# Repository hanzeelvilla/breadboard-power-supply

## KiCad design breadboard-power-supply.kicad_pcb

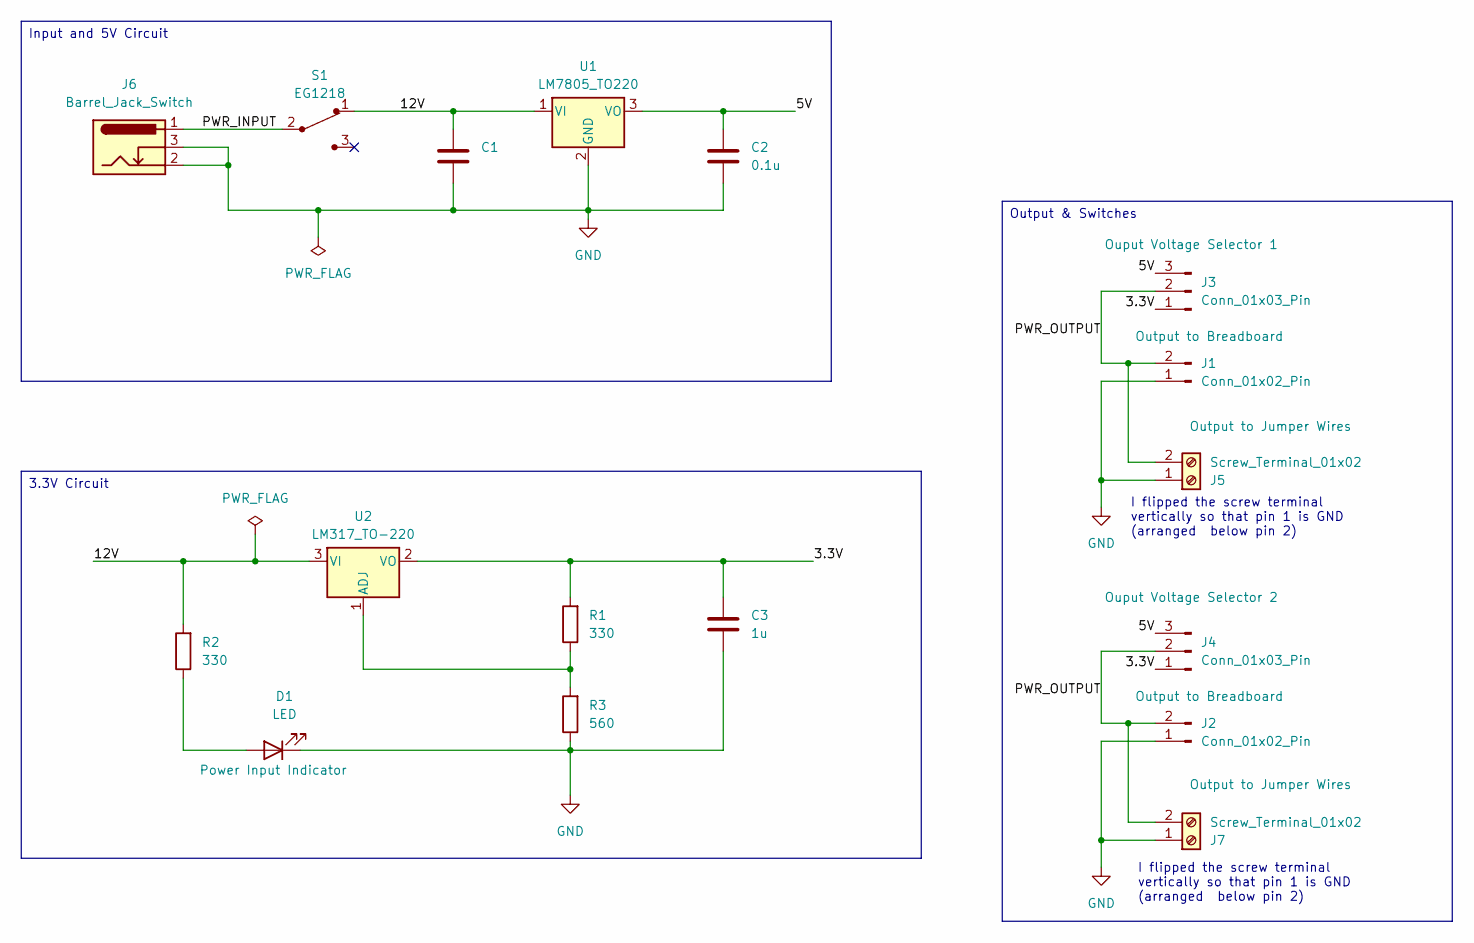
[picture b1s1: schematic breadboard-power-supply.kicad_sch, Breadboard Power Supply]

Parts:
C1: 10u; C_Disc_D3.0mm_W1.6mm_P2.50mm
C2: 0.1u; C_Disc_D3.0mm_W1.6mm_P2.50mm
C3: 1u; C_Disc_D3.0mm_W1.6mm_P2.50mm
D1: LED; LED_D5.0mm
J1, J2: Conn_01x02_Pin; PinHeader_1x02_P2.54mm_Vertical
J3, J4: Conn_01x03_Pin; PinHeader_1x03_P2.54mm_Vertical
J5, J7: Screw_Terminal_01x02; TerminalBlock_Xinya_XY308-2.54-2P_1x02_P2.54mm_Horizontal
J6: Barrel_Jack_Switch; BarrelJack_Horizontal
R1, R2: 330; R_Axial_DIN0204_L3.6mm_D1.6mm_P7.62mm_Horizontal
R3: 560; R_Axial_DIN0204_L3.6mm_D1.6mm_P7.62mm_Horizontal
S1: EG1218; Switch_Slide_11.6x4mm_EG1218; MPN EG1218; Digi-Key_PN EG1903-ND
U1: LM7805_TO220; TO-220-3_Vertical
U2: LM317_TO-220; TO-220-3_Vertical

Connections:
/3.3V: C3.1, J3.1, J4.1, R1.2, U2.2 (VO)
/5V: C2.1, J3.3, J4.3, U1.3 (VO)
/12V: C1.1, R2.2, S1.1, U1.1 (VI), U2.3 (VI)
/PWR_INPUT: J6.1, S1.2
/PWR_OUTPUT: J1.2, J2.2, J3.2, J4.2, J5.2, J7.2
GND: C1.2, C2.2, C3.2, D1.1 (K), J1.1, J2.1, J5.1, J6.2, J6.3, J7.1, R3.1, U1.2 (GND)
unnamed: D1.2 (A), R2.1
unnamed: R1.1, R3.2, U2.1 (ADJ)

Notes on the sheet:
I flipped the screw terminal vertically so that pin 1 is GND (arranged below pin 2)
Input and 5V Circuit
Output & Switches
3.3V Circuit

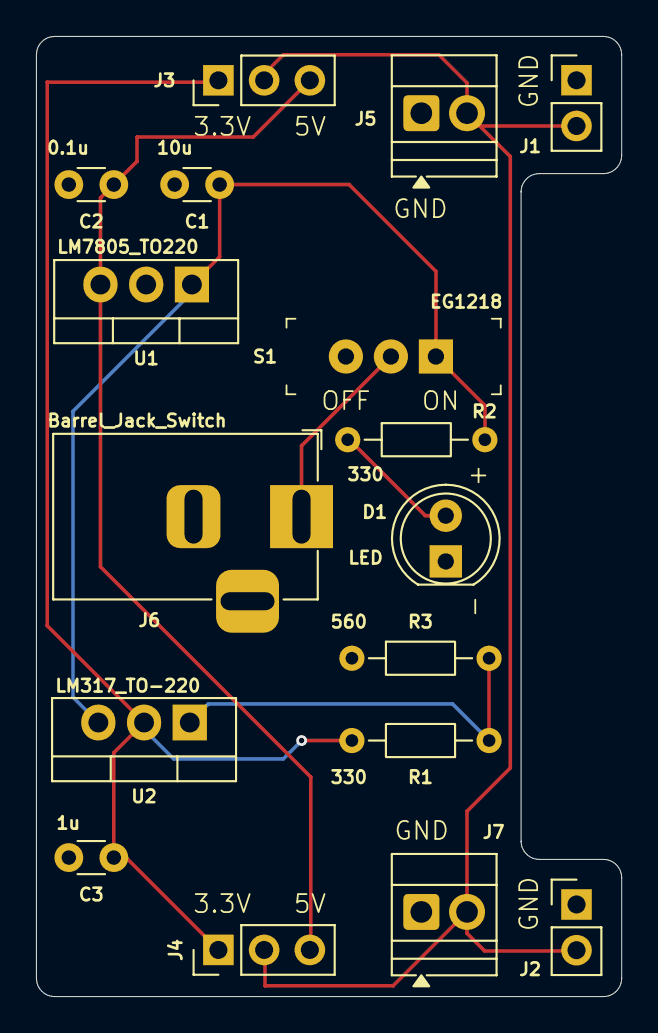
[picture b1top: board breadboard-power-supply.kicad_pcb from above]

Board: 2 copper layers, 32.5 x 53.3 mm, 17 parts (0 on the bottom side), 8 nets.

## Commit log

2025-12-18 Schema finished
2025-12-22 First PCB design
2025-12-22 PCB border refined
2025-12-24 Routes
2025-12-26 Silkscreen
